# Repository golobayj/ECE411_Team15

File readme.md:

# ECE411 Team 15 Practicum Project

## Links To Documentation:

### [Project_Design_Specification.pdf](docs/Project_Design_Specification.pdf)

### [Practicum_Project_Ideas.pdf](docs/Practicum_Project_Ideas.pdf)

### [Functional_Decomposition.pdf](docs/Functional_Decomposition.pdf)

### [Modeling.pdf](docs/Modeling.pdf)

### [Test_Plan.pdf](docs/Test_Plan.pdf)

## Final Designs:

### Demo
[Demo Video](https://drive.google.com/file/d/1zAOsdVPUFq6oVJJ1poNx3nirWUGRS5xu/view?usp=sharing)

### Schematic rev 1.1

### PCB Layout rev 1.0

### Physical Design

## Preliminary Designs:

### Breadboard

### Physical Design

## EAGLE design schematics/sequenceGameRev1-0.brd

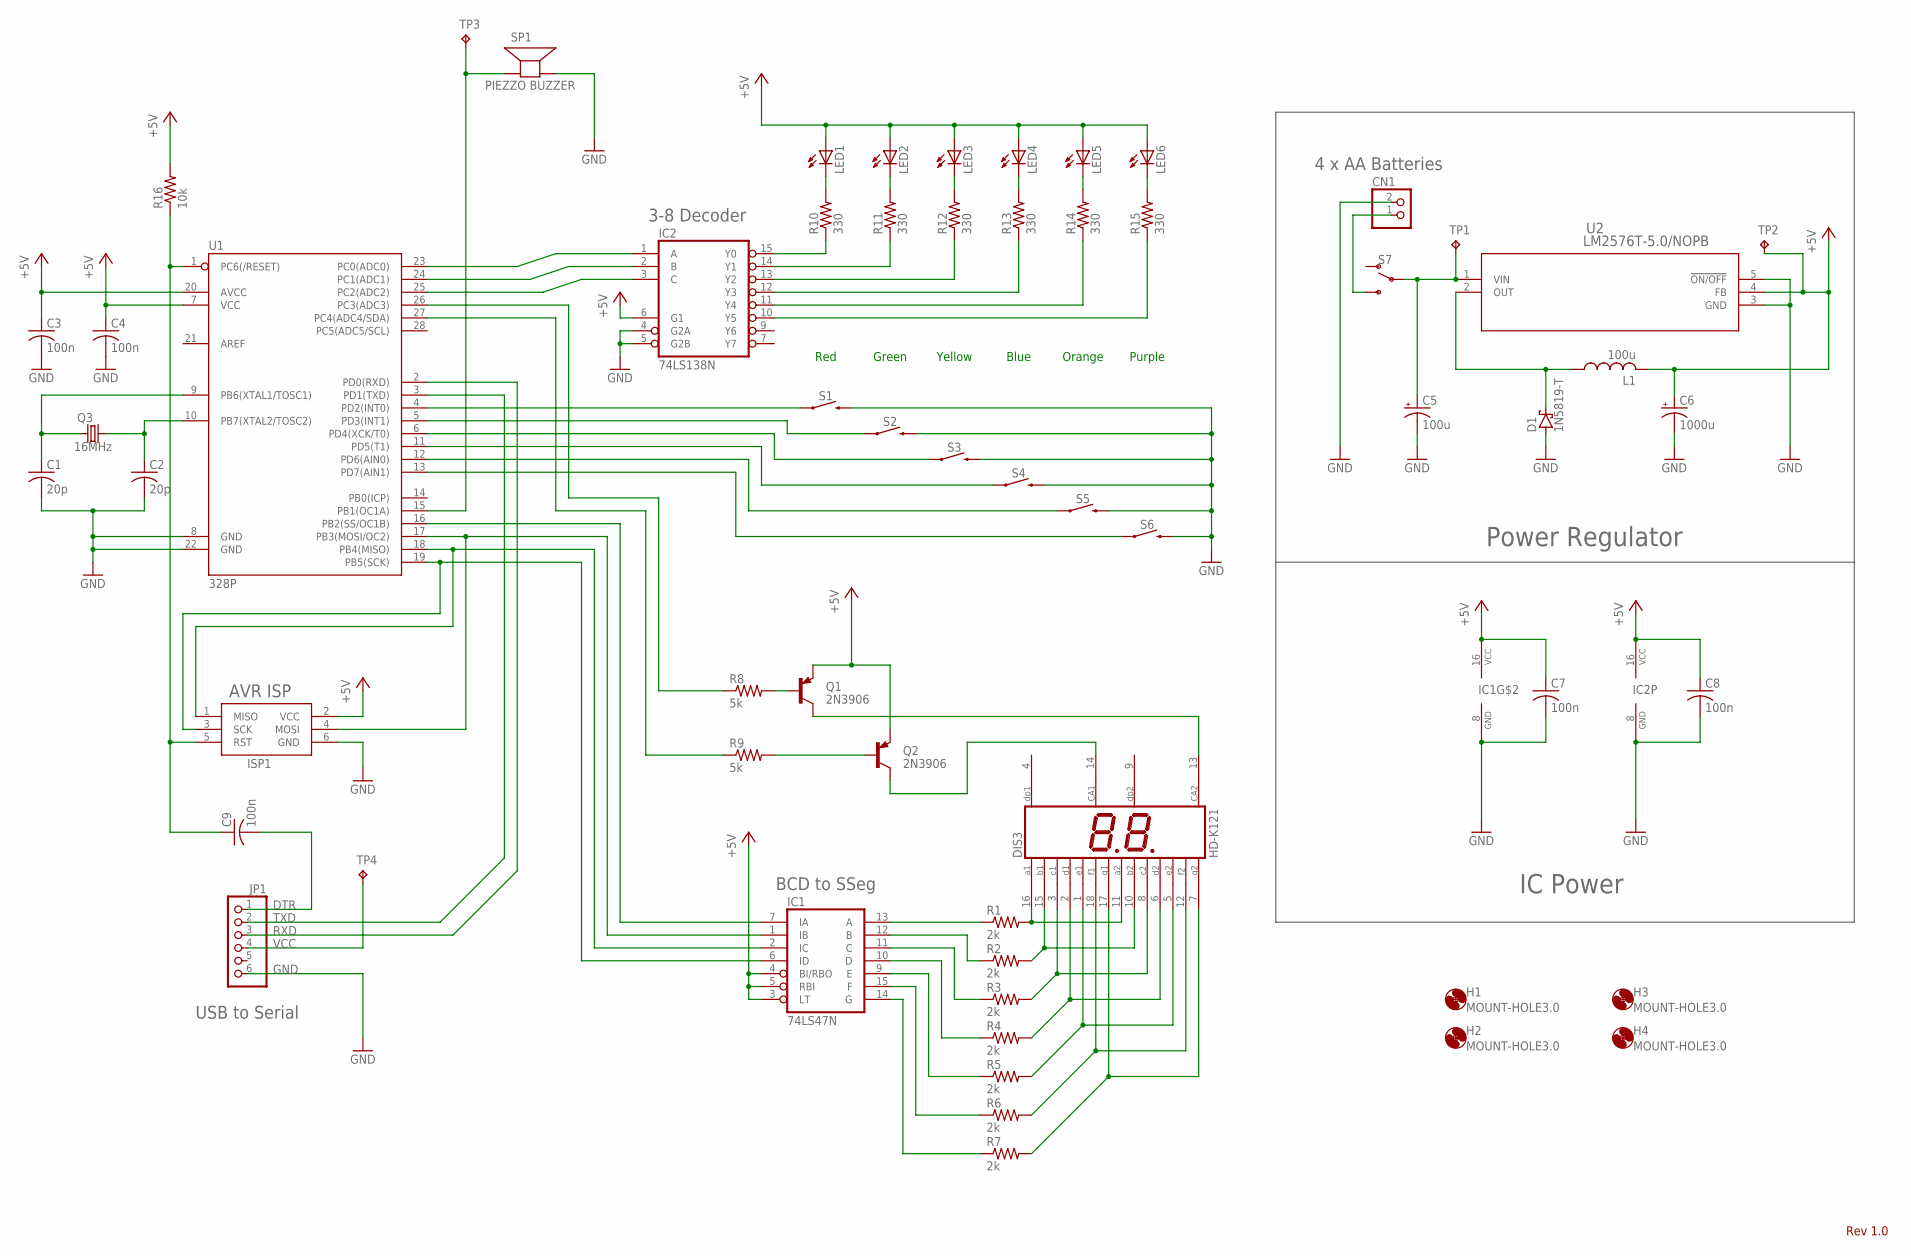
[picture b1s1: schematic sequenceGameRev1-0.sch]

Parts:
C1, C2: 20p; C050-025X075
C3, C4, C7, C8, C9: 100n; C050-025X075
C5: 100u; E2,5-5
C6: 1000u; E5-10,5
CN1: JST_2PIN-THM; JST-PH-2-THM
D1: 1N5819-T; DO41-7.6
DIS3: HD-K121; HDSP-R
H1, H2, H3, H4: MOUNT-HOLE3.0; 3,0
IC1: 74LS47N; DIL16
IC2: 74LS138N; DIL16
ISP1: AVRISP-6; AVRISP
JP1: PINHD-1X6; 1X06
L1: 100u; 0207/10
LED1, LED2, LED3, LED4, LED5, LED6: LED5MM
Q1, Q2: 2N3906; TO92
Q3: 16MHz; HC49/S
R1, R2, R3, R4, R5, R6, R7: 2k; 0207/10
R8, R9: 5k; 0207/10
R10, R11, R12, R13, R14, R15: 330; 0207/10
R16: 10k; 0207/10
S1, S2, S3, S4, S5, S6: MOMENTARY-SWITCH-SPST-PTH-6.0MM; TACTILE_SWITCH_PTH_6.0MM
S7: SWITCH-SPDT-PTH-11.6X4.0MM; SWITCH_SPDT_PTH_11.6X4.0MM
SP1: PIEZZO BUZZER; AL60P
TP1, TP2, TP3, TP4: TPB1,27; B1,27
U1: 328P; DIP28
U2: LM2576T-5.0/NOPB; T05A_TEX

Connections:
+5V: C3.1, C4.1, C6.+, C7.1, C8.1, IC1.3 (LT), IC1.4 (BI/RBO), IC1.5 (RBI), IC1.16 (VCC), IC2.6 (G1), IC2.16 (VCC), ISP1.2 (VCC), L1.2, LED1.A, LED2.A, LED3.A, LED4.A, LED5.A, LED6.A, Q1.3 (E), Q2.3 (E), R16.2, TP2.TP, U1.7 (VCC), U1.20 (AVCC), U2.4 (FB)
BATT_IN: CN1.1 (2), S7.3 (S)
DTR: C9.2, JP1.1
GND: C1.2, C2.2, C3.2, C4.2, C5.-, C6.-, C7.2, C8.2, CN1.2 (1), D1.A, IC1.8 (GND), IC2.4 (G2A), IC2.5 (G2B), IC2.8 (GND), ISP1.6 (GND), JP1.6, S1.3 (2), S2.3 (2), S3.3 (2), S4.3 (2), S5.3 (2), S6.3 (2), SP1.2 (-), U1.8 (GND), U1.22 (GND), U2.3 (GND), U2.5 (!ON/OFF)
LDO_IN: C5.+, S7.2, TP1.TP, U2.1 (VIN)
LDO_OUT: D1.C, L1.1, U2.2 (OUT)
unnamed: DIS3.10 (B2), DIS3.15 (B1), R2.2
unnamed: SP1.1 (+), TP3.TP, U1.15 (PB1(OC1A))
unnamed: DIS3.3 (C1), DIS3.8 (C2), R3.2
unnamed: DIS3.2 (D1), DIS3.6 (D2), R4.2
unnamed: DIS3.1 (E1), DIS3.5 (E2), R5.2
unnamed: DIS3.12 (F2), DIS3.18 (F1), R6.2
unnamed: IC1.13 (A), R1.1
unnamed: IC1.12 (B), R2.1
unnamed: IC1.11 (C), R3.1
unnamed: IC1.10 (D), R4.1
unnamed: IC1.9 (E), R5.1
unnamed: Q2.2 (B), R9.2
unnamed: R8.1, U1.26 (PC3(ADC3))
unnamed: Q1.2 (B), R8.2
unnamed: DIS3.7 (G2), DIS3.17 (G1), R7.2
unnamed: C2.1, Q3.1, U1.10 (PB7(XTAL2/TOSC2))
unnamed: IC2.15 (Y0), R10.1
unnamed: IC2.14 (Y1), R11.1
unnamed: IC2.13 (Y2), R12.1
unnamed: IC2.12 (Y3), R13.1
unnamed: IC2.11 (Y4), R14.1
unnamed: IC2.10 (Y5), R15.1
unnamed: C1.1, Q3.2, U1.9 (PB6(XTAL1/TOSC1))
unnamed: LED1.K (C), R10.2
unnamed: LED2.K (C), R11.2
unnamed: LED3.K (C), R12.2
unnamed: LED4.K (C), R13.2
unnamed: LED5.K (C), R14.2
unnamed: LED6.K (C), R15.2
unnamed: IC1.15 (F), R6.1
unnamed: S4.1, U1.11 (PD5(T1))
unnamed: S5.1, U1.12 (PD6(AIN0))
unnamed: IC1.6 (ID), ISP1.3 (SCK), U1.19 (PB5(SCK))
unnamed: S6.1, U1.13 (PD7(AIN1))
unnamed: IC1.2 (IC), ISP1.1 (MISO), U1.18 (PB4(MISO))
unnamed: S2.1, U1.5 (PD3(INT1))
unnamed: IC2.1 (A), U1.23 (PC0(ADC0))
unnamed: IC2.2 (B), U1.24 (PC1(ADC1))
unnamed: S3.1, U1.6 (PD4(XCK/T0))
unnamed: IC1.7 (IA), U1.16 (PB2(SS/OC1B))
unnamed: IC1.1 (IB), ISP1.4 (MOSI), U1.17 (PB3(MOSI/OC2))
unnamed: R9.1, U1.27 (PC4(ADC4/SDA))
unnamed: DIS3.13 (CA2), Q1.1 (C)
unnamed: IC2.3 (C), U1.25 (PC2(ADC2))
unnamed: DIS3.14 (CA1), Q2.1 (C)
unnamed: DIS3.11 (A2), DIS3.16 (A1), R1.2
unnamed: IC1.14 (G), R7.1
unnamed: S1.1, U1.4 (PD2(INT0))
RESET: C9.1, ISP1.5 (RST), R16.1, U1.1 (PC6(/RESET))
RXD: JP1.3, U1.2 (PD0(RXD))
TXD: JP1.2, U1.3 (PD1(TXD))
VCC: JP1.4, TP4.TP

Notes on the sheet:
Red
Green
Yellow
Blue
Orange
Purple
3-8 Decoder
BCD to SSeg
4 x AA Batteries
AVR ISP
USB to Serial
Power Regulator
IC Power
Rev 1.0

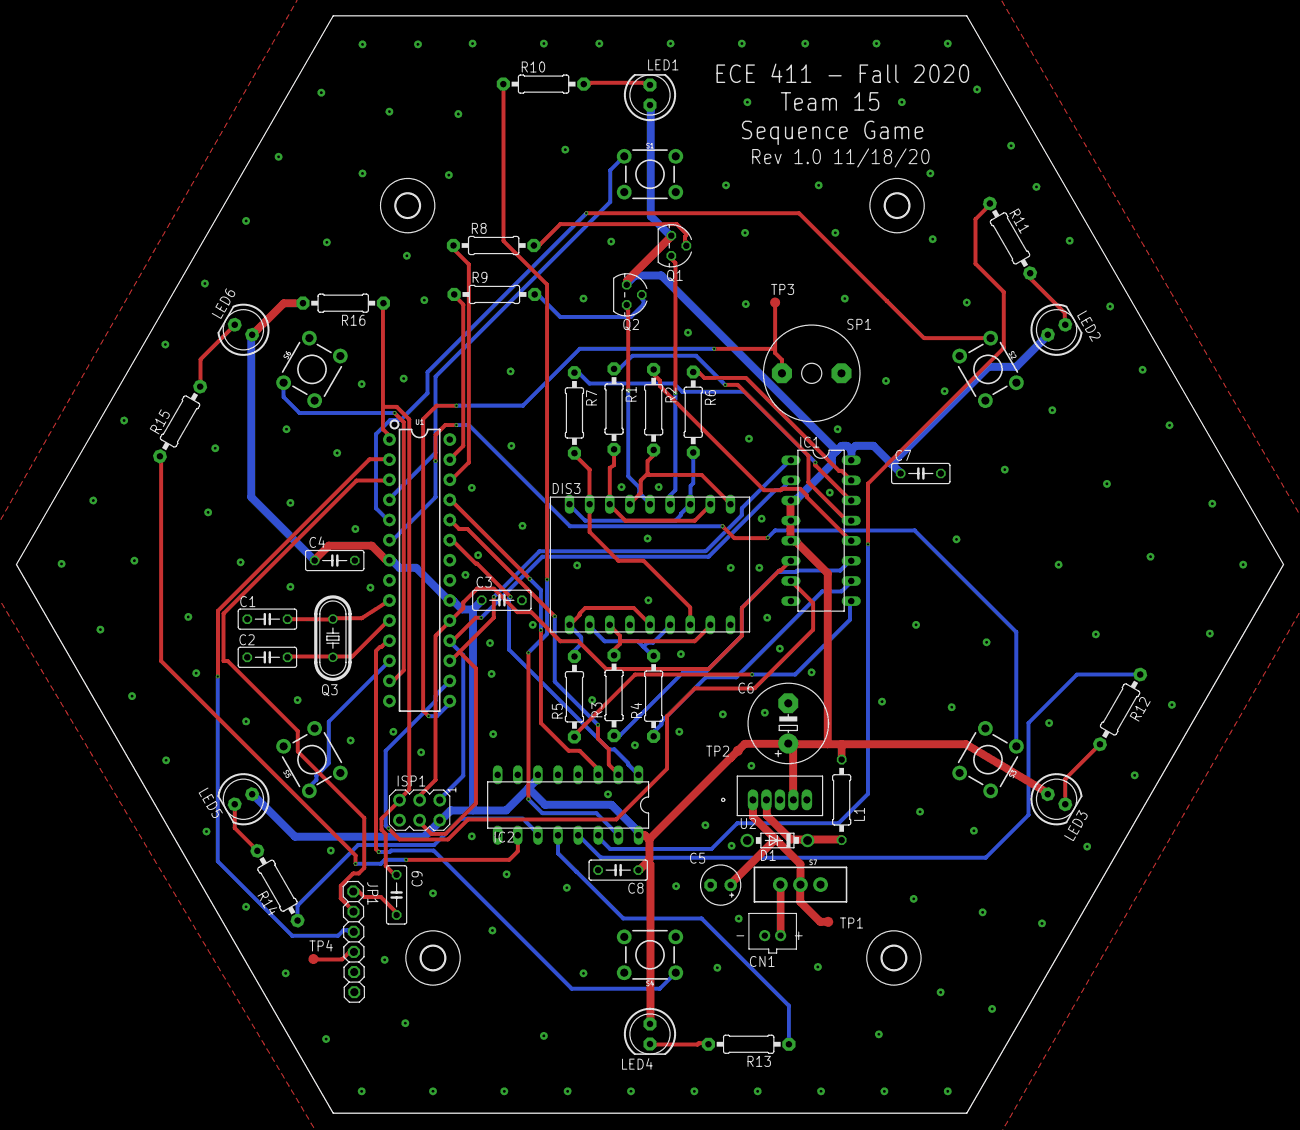
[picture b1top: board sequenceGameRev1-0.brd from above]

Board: 2 copper layers, 160.0 x 138.6 mm, 60 parts (0 on the bottom side), 58 nets.

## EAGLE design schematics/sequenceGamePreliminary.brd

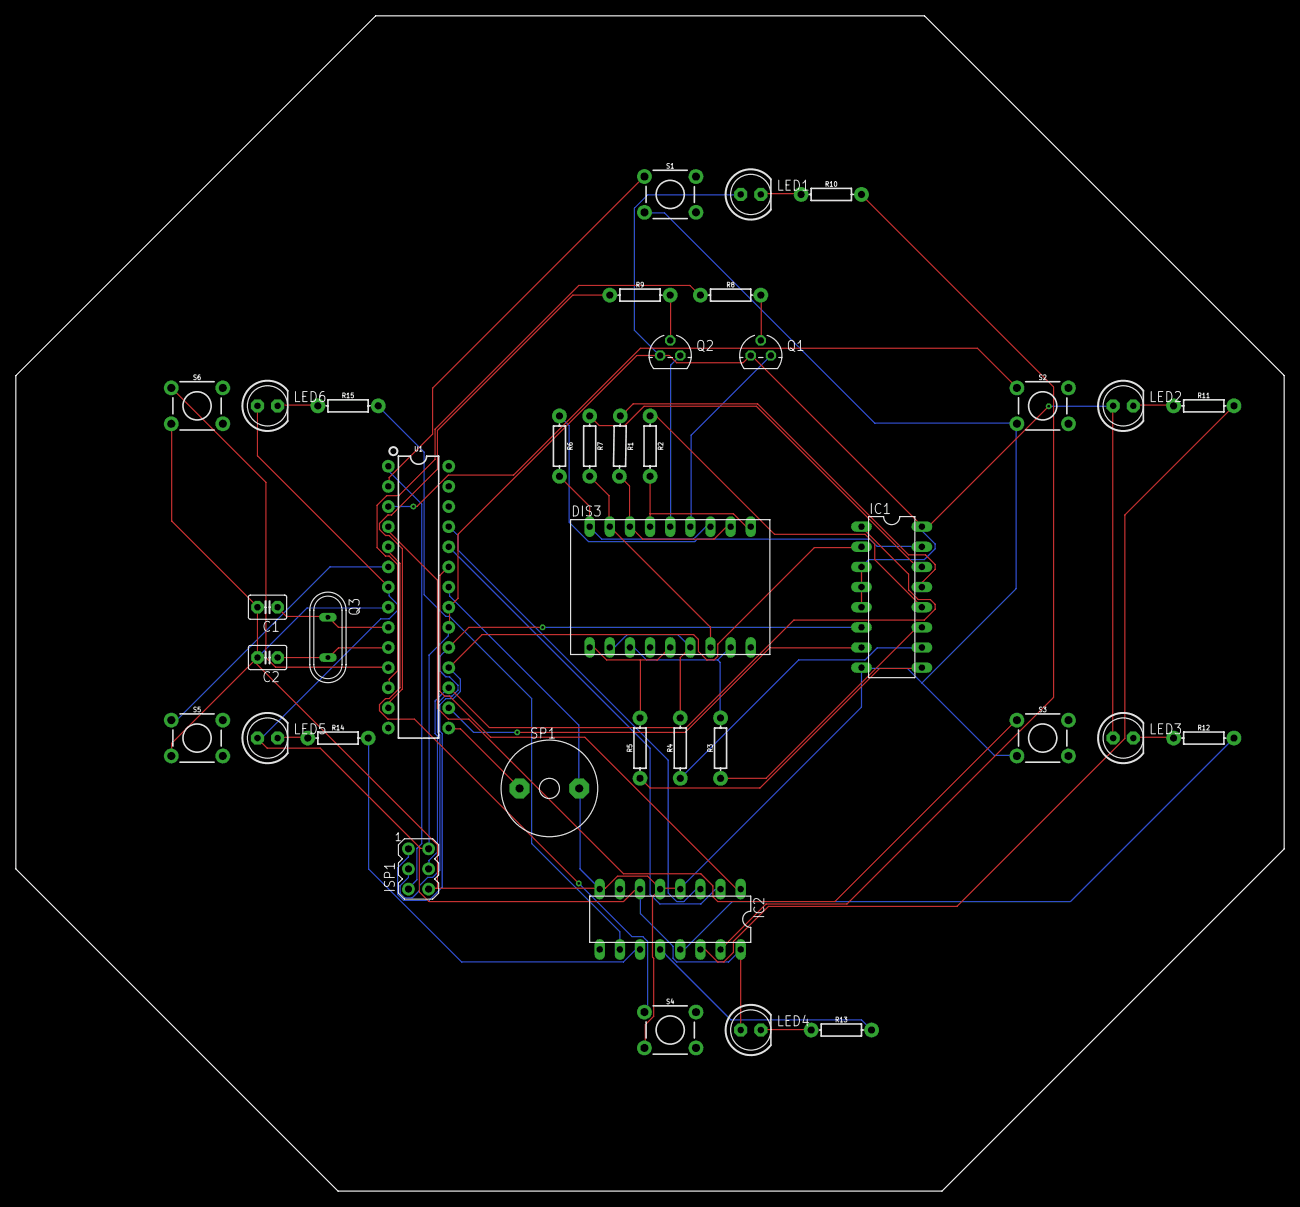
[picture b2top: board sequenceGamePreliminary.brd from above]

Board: 2 copper layers, 160.0 x 148.3 mm, 38 parts (0 on the bottom side), 51 nets.

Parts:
C1, C2: 20p; C2.5-3
DIS3: HD-K121; HDSP-R
IC1: 74LS47N; DIL16
IC2: 74LS138N; DIL16
ISP1: AVRISP-6; AVRISP
LED1, LED2, LED3, LED4, LED5, LED6: LED5MM
Q1, Q2: 2N3906; TO92
Q3: QS
R1, R2, R3, R4, R5, R6, R7, R8, R9, R10, R11, R12, R13, R14, R15: AXIAL-0.3
S1, S2, S3, S4, S5, S6: MOMENTARY-SWITCH-SPST-PTH-6.0MM; TACTILE_SWITCH_PTH_6.0MM
SP1: SPEAKER/AL60P; AL60P
U1: 328P; DIP28

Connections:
+5V: IC1.3, IC1.4, IC1.5, IC1.16, IC2.6, IC2.16, ISP1.2, LED1.A, LED2.A, LED3.A, LED4.A, LED5.A, LED6.A, Q1.3, Q2.3, U1.7, U1.20, U1.21
GND: C1.2, C2.2, IC1.8, IC2.4, IC2.5, IC2.8, ISP1.6, S1.3, S2.3, S3.3, S4.3, S5.3, S6.3, SP1.2, U1.8, U1.22
unnamed: DIS3.10, DIS3.15, R2.P$2
unnamed: SP1.1, U1.15
unnamed: DIS3.3, DIS3.8, R3.P$2
unnamed: DIS3.2, DIS3.6, R4.P$2
unnamed: DIS3.1, DIS3.5, R5.P$2
unnamed: DIS3.12, DIS3.18, R6.P$2
unnamed: IC1.13, R1.P$1
unnamed: IC1.12, R2.P$1
unnamed: IC1.11, R3.P$1
unnamed: IC1.10, R4.P$1
unnamed: IC1.9, R5.P$1
unnamed: Q2.2, R9.P$2
unnamed: R8.P$1, U1.12
unnamed: Q1.2, R8.P$2
unnamed: DIS3.7, DIS3.17, R7.P$2
unnamed: C2.1, Q3.2, U1.10
unnamed: IC2.15, R10.P$2
unnamed: IC2.14, R11.P$2
unnamed: IC2.13, R12.P$2
unnamed: IC2.12, R13.P$2
unnamed: IC2.11, R14.P$2
unnamed: IC2.10, R15.P$2
unnamed: C1.1, Q3.1, U1.9
unnamed: LED1.K, R10.P$1
unnamed: LED2.K, R11.P$1
unnamed: LED3.K, R12.P$1
unnamed: LED4.K, R13.P$1
unnamed: LED5.K, R14.P$1
unnamed: LED6.K, R15.P$1
unnamed: IC1.15, R6.P$1
unnamed: S4.1, U1.5
unnamed: S5.1, U1.6
unnamed: IC1.6, ISP1.3, U1.19
unnamed: ISP1.5, U1.1
unnamed: S6.1, U1.11
unnamed: S1.1, U1.2
unnamed: IC1.2, ISP1.1, U1.18
unnamed: S2.1, U1.3
unnamed: IC2.1, U1.23
unnamed: IC2.2, U1.24
unnamed: S3.1, U1.4
unnamed: IC1.7, U1.16
unnamed: IC1.1, ISP1.4, U1.17
unnamed: R9.P$1, U1.13
unnamed: DIS3.13, Q1.1
unnamed: IC2.3, U1.25
unnamed: DIS3.14, Q2.1
unnamed: DIS3.11, DIS3.16, R1.P$2
unnamed: IC1.14, R7.P$1

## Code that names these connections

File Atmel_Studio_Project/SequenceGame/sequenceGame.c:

/*
 * sequenceGame.c
 *
 * Author : Jon Golobay
 */ 
#ifndef F_CPU					// if F_CPU was not defined in Project -> Properties
#define F_CPU 16000000UL		// define it now as 16 MHz unsigned long
#endif

#include <avr/io.h>
#include <avr/interrupt.h>
#include <util/delay.h>	
#include "sevenSegment.h"

#define ledA PC0
#define ledB PC1
#define ledC PC2

#define digit0 PC3
#define digit1 PC4

#define sSegA PB2	
#define sSegB PB3	
#define sSegC PB4
#define sSegD PB5

#define buttonPur PD2
#define buttonYel PD3
#define buttonRed PD4		
#define buttonBlu PD5
#define buttonGre PD6
#define buttonOra PD7

#define speaker PB1

enum color{PURPLE, YELLOW, RED, BLUE, GREEN, ORANGE, OFF};
enum state{idle, start, playSequence, inputSequence, win, lose};
	
static uint8_t randomSeed = 0, *randomSeedPtr = &randomSeed;

volatile uint8_t toneCount = 0xFF, *toneCountPtr = &toneCount;

static enum state gameState = idle;
volatile static enum color input, lastInput;
volatile uint8_t roundCount = 0;
volatile uint8_t inputCounter = 0;

#define MAX_SEQ_LENGTH 5
uint8_t randomSequence[MAX_SEQ_LENGTH];

sSeg_t disp = {sSegA, sSegB, sSegC, sSegD, digit0, digit1, 0, 0, 0};

// Function Prototypes
void driveOutput(enum color col);
void displaySequence(int length, uint8_t sequence[]);
enum state acceptInput(uint8_t length);
void generateSequence(uint8_t length, uint8_t *seed);
void seedSequence(uint8_t *seed);
void toneOn(uint8_t count);
void toneOff(void);

int main(void)
{	
	// setup speaker as output
	DDRB |= (1 << speaker);
	
	// setup timer 1 for speaker
	TCCR1A = 0x00; // Normal operation
	TCCR1B = (1<<CS11)|(1<<CS10)|(1<<WGM12)|(1<<ICNC1); // 256x prescaler, MODE 4
	TCCR1C = 0x80;

	// Setup seven segment display outputs
	DDRC |= (1 << digit0) | (1 << digit1);
	DDRB |= (1 << sSegA) | (1 << sSegB) | (1 << sSegC) | (1 << sSegD);
	PORTB |= (1 << sSegA) | (1 << sSegB) | (1 << sSegC) | (1 << sSegD);

	// setup timer 2 for seven segment time division multiplexing
	TCCR2A = 0b00000010;
	TCCR2B = 0b00000101;
	TIMSK2 = 0b00000010;
	OCR2A = 0b01000100;
		
	// setup buttons as inputs with pull-ups
	DDRD &= ~(1 << buttonPur) | ~(1 << buttonYel) | ~(1 << buttonRed) | ~(1 << buttonBlu) | ~(1 << buttonGre) | ~(1 << buttonOra);
	PORTD |= (1 << buttonPur) | (1 << buttonYel) | (1 << buttonRed) | (1 << buttonBlu) | (1 << buttonGre) | (1 << buttonOra);

	// enable button interrupts
	PCMSK2 |= (1 << PCINT18) | (1 << PCINT19) | (1 << PCINT20) | (1 << PCINT21) | (1 << PCINT22) | (1 << PCINT23);
	
	// LED SETUP
	// setup led decoder outputs
	DDRC |= (1 << ledA) | (1 << ledB) | (1 << ledC);
		
	// enable global interrupts
	sei();
	
	//seed random sequence generator at power on
	seedSequence(randomSeedPtr);
	
	while (1)
	{	
		while (gameState == idle) {
			roundCount = 0;
			//enable button interrupts
			PCICR |= (1 << PCIE2);
			driveOutput(OFF);
			setDisplayValue(roundCount,&disp);
			toneOff();
		}
		while (gameState == start) {
			generateSequence(MAX_SEQ_LENGTH, randomSeedPtr);
			gameState = playSequence;
		}
		while (gameState == playSequence) {
			//disable button interrupts
			PCICR &= ~(1 << PCIE2);
			setDisplayValue(roundCount,&disp);
			displaySequence(roundCount+1, randomSequence);
			gameState = inputSequence;
		}
		while (gameState == inputSequence) {
			//enable button interrupts
			PCICR |= (1 << PCIE2);
			gameState = acceptInput(roundCount+1);
		}
		while (gameState == win) {
			setDisplayValue(roundCount,&disp);
			_delay_ms(100);
			for(int i=0; i<3; i++) {
				driveOutput(PURPLE);
				_delay_ms(200);
				driveOutput(BLUE);
				_delay_ms(200);
				driveOutput(YELLOW);
				_delay_ms(200);
				driveOutput(GREEN);
				_delay_ms(200);
				driveOutput(RED);
				_delay_ms(200);
				driveOutput(ORANGE);
				_delay_ms(200);
			}
			gameState = idle;
		}
		while (gameState == lose) {
			TCCR1A = 0x03; 
			toneOn(0xFF);
			_delay_ms(2500);
			toneOff();
			TCCR1A = 0x00;
			gameState = idle;
		}
	}
	return 0;
	
	
}


void displaySequence(int length, uint8_t sequence[]){
	//loop through and display length of sequence
	for(int i=0; i < length; i++){
		driveOutput(OFF);
		_delay_ms(100);
		driveOutput(sequence[i]);
		_delay_ms(1000);
	}
	driveOutput(OFF);
	_delay_ms(100);
}

enum state acceptInput(uint8_t length){
	
	inputCounter = 0;
	uint8_t i = 0;

	while(i < length) {
		lastInput = OFF;
		while(inputCounter <= 20) {
			_delay_ms(100);  // 100 works good here for play, 1000 for testing
			inputCounter++;
			//setDisplayValue(inputCounter, &disp);
			if(lastInput == randomSequence[i]){
				inputCounter=0;
				i++;
				_delay_ms(100);
				if(length == MAX_SEQ_LENGTH  && i == length) {
					roundCount++;
					_delay_ms(1000);
					driveOutput(OFF);
					_delay_ms(1000);
					return win;
				}
				if(i == length) {
					roundCount++;
					_delay_ms(1000);
					driveOutput(OFF);
					_delay_ms(1000);
					return playSequence;
				}
				break;
			}
			else if(inputCounter == 5) driveOutput(OFF);
			else if(inputCounter >= 20) return lose;
			else if(lastInput != randomSequence[i] && lastInput != OFF) return lose;
		}
		inputCounter=0;
	}
	_delay_ms(500);
	return playSequence;
}


void driveOutput(enum color col) {
	switch (col) {
		case(PURPLE):	// 000
			toneOn(0x80);
			PORTC  &= ~((1 << ledC) | (1 << ledB) | (1 << ledA));
			break;
		case(YELLOW):	// 001
			toneOn(0x70);
			PORTC  |= (1 << ledA);
			PORTC  &= ~((1 << ledB) | (1 << ledC));
			break;
		case(RED):		// 010
			toneOn(0x60);
			PORTC  |= (1 << ledB);
			PORTC  &= ~((1 << ledC) | (1 << ledA));
			break;
		case(BLUE):		// 011
			toneOn(0x50);
			PORTC  |= ((1 << ledB) | (1 << ledA));
			PORTC  &= ~(1 << ledC);
			break;
		case(GREEN):	// 100
			toneOn(0x40);
			PORTC  |= (1 << ledC) ;
			PORTC  &= ~((1 << ledB) | (1 << ledA));
			break;
		case(ORANGE):	// 101
			toneOn(0x30);
			PORTC  |= ((1 << ledC) | (1 << ledA));
			PORTC  &= ~(1 << ledB);
			break;
		case(OFF):		// 111
			PORTC  |= ((1 << ledC) | (1 << ledB) | (1 << ledA));
			toneOff();
			break;
	}
}


void seedSequence(uint8_t *seed){
	*seed = 1;
	uint8_t ADCval;

	ADMUX = 5;         // use ADC5
	ADMUX |= (1 << REFS0);    // use AVcc as the reference
	ADMUX &= ~(1 << ADLAR);   // clear for 10 bit resolution
		
	ADCSRA |= (1 << ADPS2) | (1 << ADPS1) | (1 << ADPS0);    // 128 prescale 
	ADCSRA |= (1 << ADEN);    // Enable the ADC

	ADCSRA |= (1 << ADSC);    // Start the ADC conversion

	while(ADCSRA & (1 << ADSC));      // Waits for ADC to finish conversion

	ADCval = ADCL;
	ADCval = (ADCH << 8) + ADCval;    // ADCH is read so ADC can be updated again
	ADCSRA &= ~(1 << ADEN);  //disable the ADC
	*seed = ADCval;
}

void generateSequence(uint8_t length, uint8_t *seed){
	for(int i=0; i<length; i++) {
		*seed ^= (*seed << 7);
		*seed ^= (*seed >> 5);
		*seed ^= (*seed << 3);
		randomSequence[i] = *seed % 6;
	}
}

void toneOn(uint8_t count)
{	
	OCR1A = count;
	TIMSK1 |= (1 << OCIE1A);
}

void toneOff(void)
{
	// disable timer1 interrupts to stop tone
	TIMSK1 &= (~1 << OCIE1A);
}


ISR(TIMER2_COMPA_vect) {
	displayDigits(&disp);
}

ISR(TIMER1_COMPA_vect)
{
	PORTB ^= (1 << speaker);
}

ISR(PCINT2_vect) {
	if(gameState == idle) gameState = start;
	else if(gameState == inputSequence  && inputCounter != 0) {
		if(!(PIND & (1 << buttonPur))) {
			input = PURPLE;
			lastInput = PURPLE;
		}
		else if(!(PIND & (1 << buttonYel))) {
			input = YELLOW;
			lastInput = YELLOW;
		}
		else if(!(PIND & (1 << buttonRed))) {
			input = RED;
			lastInput = RED;

		}
		else if(!(PIND & (1 << buttonBlu))) {
			input = BLUE;
			lastInput = BLUE;
		}
		else if(!(PIND & (1 << buttonGre))) {
			input = GREEN;
			lastInput = GREEN;
		}
		else if(!(PIND & (1 << buttonOra))) {
			input = ORANGE;
			lastInput = ORANGE;
		}
		else {
			input = OFF;
		}
		driveOutput(input);
	}
}

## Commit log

2020-10-15 Added which project the team selected
2020-10-26 added Project Design Specification
2020-10-26 Create LICENSE
2020-10-26 added L1 decomp and preliminary physical design
2020-10-26 Add links to design documents and embedded images
2020-11-02 added preliminarySchematic
2020-11-02 added preliminary design images
2020-11-02 Added preliminary schematic and breadboard
2020-11-02 added audio amp and speaker
2020-11-09 added preliminary PCB layout
2020-11-10 added atmel studio project includes src code
2020-11-12 added project schedule
2020-11-12 added preliminary bill of materials
2020-11-14 added latest version of schedule
2020-11-19 added rev 1.0 of schematic and board sent to OSH Park
2020-11-19 added images of rev 1.0 schematic and board
2020-11-19 updated readme with rev 1.0 board and schematic
2020-11-21 added functional decomp
2020-11-21 updated readme with functional decomp
2020-11-28 added modeling.pdf(UML class and state diagrams)
2020-12-02 updated schematic to new color arrangement
2020-12-02 Color update on schematic
2020-12-08 added Test Plan
2020-12-08 added final code revision
2020-12-08 Fixed link to demo video

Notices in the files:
parts and their libraries:
SparkFun-Resistors: Licensing: Creative Commons ShareAlike 4.0 International - https://creativecommons.org/licenses/by-sa/4.0
COPYRIGHT: Copyright (C) 2018 Accelerated Designs. All rights reserved
